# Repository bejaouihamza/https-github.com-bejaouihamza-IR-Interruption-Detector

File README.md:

# 🔦 IR Interruption Detector PCB

This project is a complete PCB-based system that detects interruptions between an **IR emitter and receiver**. When an object blocks the IR beam:
- A **buzzer/speaker** is triggered,
- A **7-segment display counter** is incremented,
- A **reset button** clears the count.

The circuit is entirely based on **discrete components**, including **NE555 timers**, **CD40106**, and a **CD4033** counter/decoder. It also includes a **robust regulated power supply**, and can be used in security, object-counting, or automation systems.

---

## 📷 Schematic

---

## 🧩 PCB Layout

---

## 🧱 3D Model

---

## ⚙️ System Overview

### ➤ Power Supply
The power input is **230V AC**, stepped down using a transformer and rectified via a **bridge diode**. The output is regulated to **+12V DC** using a **7812 voltage regulator**.

---

### ➤ IR Transmitter Stage

- **Components**: 2x NE555 + TSAL4400 IR LED
- The first NE555 generates a **square wave** (~38 kHz), modulated by the second NE555 to create an **amplitude-modulated IR beam**.
- Transistor **Q1** amplifies the signal and drives the IR LED with enough current.

---

### ➤ IR Receiver & Detection

- **TSOP2254** is used to receive the modulated IR beam.
- Its digital output goes **LOW** when it detects the 38 kHz signal.
- When an interruption occurs (e.g. hand/object blocks the beam), the output goes **HIGH**, triggering further stages.

---

### ➤ Signal Conditioning & Alarm Logic

- NE555 (U6) is configured in a monostable mode.
- CD40106 Schmitt triggers (U2, U3) are used for **clean signal shaping** and logic handling.
- This ensures only valid interruptions trigger the output.

---

### ➤ Output Stage

- A speaker or buzzer (AST-1732MR-R) is triggered via transistor Q3.
- An LED also indicates the alarm visually.

---

### ➤ Counting Stage

- A **CD4033B** 7-segment BCD counter increments with each IR interruption.
- A **D168K** display shows the count.
- A reset button allows clearing the count manually.

---

## 🔁 Workflow Summary

1. **Idle**: IR signal is received, no object interrupting.
2. **Interrupt**: Object breaks the beam → TSOP output goes HIGH.
3. **Detection**: NE555 monostable timer triggers.
4. **Alarm**: Buzzer sounds + 7segments Display increments count.
5. **Reset**: Pressing the reset button clears the counter.

---

## 🧰 Bill of Materials (BOM)

| Component     | Quantity | Notes                              |
|---------------|----------|------------------------------------|
| NE555         | 3        | Signal modulation and detection    |
| TSOP2254      | 1        | IR receiver                        |
| TSAL4400      | 1        | IR LED                             |
| CD40106       | 1        | Schmitt trigger inverter           |
| CD4033B       | 1        | BCD Counter                        |
| D168K         | 1        | 7-Segment Display                  |
| AST-1732MR-R  | 1        | Buzzer/Speaker                     |
| Q1, Q2, Q3    | 3        | NPN transistors                    |
| TP4056        | 1 (opt.) | Optional for battery version       |
| AMS1117-3.3   | 1 (opt.) | Optional for low-voltage designs   |

---

## 🔧 Tools Used

- **KiCad 9** for schematic and PCB design
- **Open source components**
- **Through-hole components **

---

## 🧠 Author

Designed by **Bejaoui Hamza**  
Date: **18 June 2025**  
Project name: `IR Interruption Detector`

---

## 📂 License

This project is open-source under the [MIT License](LICENSE).

---

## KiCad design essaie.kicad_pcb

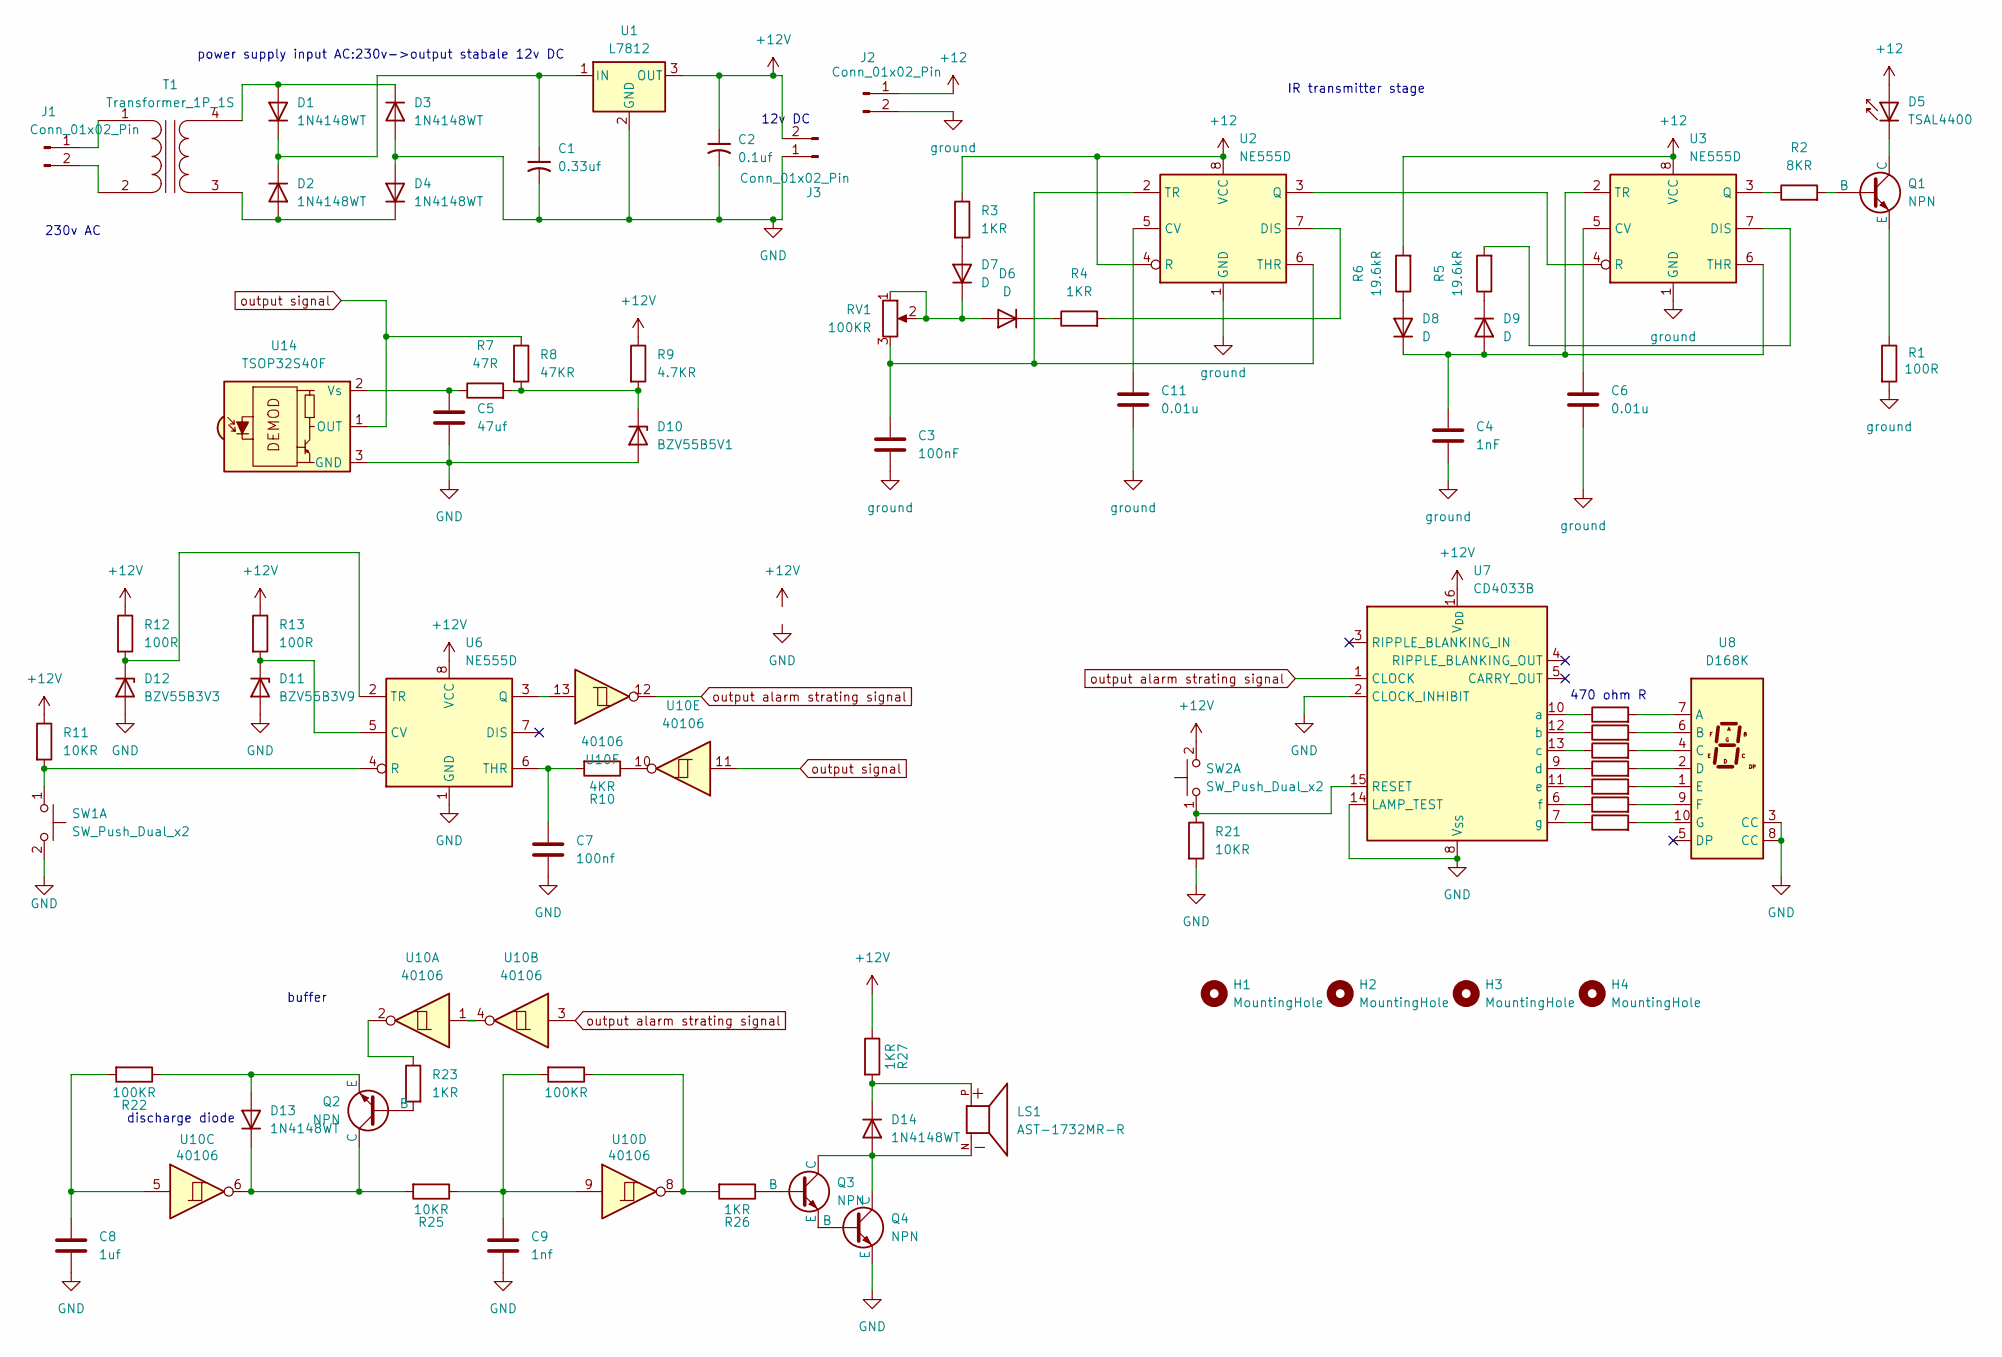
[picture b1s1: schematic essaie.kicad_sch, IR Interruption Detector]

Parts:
C1: 0.33uf; CP_Radial_D5.0mm_P2.50mm
C2: 0.1uf; CP_Radial_D5.0mm_P2.50mm
C3: 100nF; CP_Radial_D5.0mm_P2.50mm
C4: 1nF; CP_Radial_D4.0mm_P1.50mm
C5: 47uf; CP_Radial_D8.0mm_P3.50mm
C6, C11: 0.01u; CP_Radial_D4.0mm_P1.50mm
C7: 100nf; CP_Radial_D5.0mm_P2.50mm
C8: 1uf; CP_Radial_D5.0mm_P2.50mm
C9: 1nf; CP_Radial_D5.0mm_P2.50mm
D1, D2, D3, D4: 1N4148WT; D_5W_P10.16mm_Horizontal
D5: TSAL4400; LED_D3.0mm_IRBlack
D6, D7, D8, D9: D; D_DO-35_SOD27_P10.16mm_Horizontal
D10: BZV55B5V1; D_DO-35_SOD27_P10.16mm_Horizontal
D11: BZV55B3V9; D_DO-35_SOD27_P10.16mm_Horizontal
D12: BZV55B3V3; D_DO-35_SOD27_P10.16mm_Horizontal
D13, D14: 1N4148WT; D_DO-35_SOD27_P10.16mm_Horizontal
H1, H2, H3, H4: MountingHole; MountingHole_2.5mm_Pad_Via
J1, J2, J3: Conn_01x02_Pin; JST_EH_B2B-EH-A_1x02_P2.50mm_Vertical
LS1: AST-1732MR-R; SPKR_AST-1732MR-R; PARTREV C
Q1, Q2, Q3, Q4: NPN; TO-92_Inline
R1, R12, R13: 100R; R_Axial_DIN0207_L6.3mm_D2.5mm_P7.62mm_Horizontal
R2: 8KR; R_Axial_DIN0207_L6.3mm_D2.5mm_P7.62mm_Horizontal
R3, R4, R23, R26, R27: 1KR; R_Axial_DIN0207_L6.3mm_D2.5mm_P7.62mm_Horizontal
R5, R6: 19.6kR; R_Axial_DIN0207_L6.3mm_D2.5mm_P7.62mm_Horizontal
R7: 47R; R_Axial_DIN0207_L6.3mm_D2.5mm_P7.62mm_Horizontal
R8: 47KR; R_Axial_DIN0207_L6.3mm_D2.5mm_P7.62mm_Horizontal
R9: 4.7KR; R_Axial_DIN0207_L6.3mm_D2.5mm_P7.62mm_Horizontal
R10: 4KR; R_Axial_DIN0207_L6.3mm_D2.5mm_P7.62mm_Horizontal
R11, R21, R25: 10KR; R_Axial_DIN0207_L6.3mm_D2.5mm_P7.62mm_Horizontal
R14, R15, R16, R17, R18, R19, R20: R; R_Axial_DIN0207_L6.3mm_D2.5mm_P7.62mm_Horizontal
R22, R24: 100KR; R_Axial_DIN0207_L6.3mm_D2.5mm_P7.62mm_Horizontal
RV1: 100KR; Potentiometer_Bourns_3266W_Vertical
SW1, SW2: SW_Push_Dual_x2; SW_FSM8JH
T1: Transformer_1P_1S; Transformer_37x44
U1: L7812; TO-220-3_Vertical
U2, U3, U6: NE555D; DIP-8_W7.62mm
U7: CD4033B; DIP-16_W7.62mm
U8: D168K; D1X8K
U10: 40106; DIP-14_W10.16mm
U14: TSOP32S40F; Vishay_MOLD-3Pin

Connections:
+12: D5.2 (A), J2.1, R3.1, R6.2, U2.4 (R), U2.8 (VCC), U3.8 (VCC)
+12V: C2.1, J3.2, R9.1, R11.1, R12.1, R13.1, R27.1, SW2.2 (D), U1.3 (OUT), U6.8 (VCC), U7.16 (V_{DD})
GND: C1.2, C2.2, C5.2, C7.2, C8.2, C9.2, D3.2 (A), D4.2 (A), D10.2 (A), D11.2 (A), D12.2 (A), J3.1, Q4.3 (E), R21.2, SW1.2 (D), U1.2 (GND), U6.1 (GND), U7.2 (CLOCK_INHIBIT), U7.8 (V_{SS}), U7.14 (LAMP_TEST), U8.3 (CC), U8.8 (CC), U14.3 (GND)
unnamed: C8.1, R22.2, U10.5
unnamed: C9.1, R24.2, R25.1, U10.9
unnamed: D1.2 (A), D3.1 (K), T1.4 (SB)
unnamed: C1.1, D1.1 (K), D2.1 (K), U1.1 (IN)
unnamed: D2.2 (A), D4.1 (K), T1.3 (SA)
unnamed: D5.1 (K), Q1.1 (C)
unnamed: D6.2 (A), D7.1 (K), RV1.1, RV1.2
unnamed: D6.1 (K), R4.1
unnamed: D7.2 (A), R3.2
unnamed: D8.2 (A), R6.1
unnamed: C4.1, D8.1 (K), D9.2 (A), U3.2 (TR), U3.6 (THR)
unnamed: D9.1 (K), R5.1
unnamed: D10.1 (K), R7.2, R8.2, R9.2
unnamed: D11.1 (K), R13.2, U6.5 (CV)
unnamed: D12.1 (K), R12.2, U6.2 (TR)
unnamed: D13.2 (A), Q2.3 (E), R22.1
unnamed: D13.1 (K), Q2.1 (C), R25.2, U10.6
unnamed: D14.2 (A), LS1.N, Q3.1 (C), Q4.1 (C)
unnamed: D14.1 (K), LS1.P, R27.2
unnamed: J1.1, T1.1 (AA)
unnamed: J1.2, T1.2 (AB)
unnamed: Q1.2 (B), R2.2
unnamed: Q1.3 (E), R1.1
unnamed: Q2.2 (B), R23.2
unnamed: Q3.2 (B), R26.1
unnamed: Q3.3 (E), Q4.2 (B)
unnamed: R10.1, U10.10
unnamed: R23.1, U10.2
unnamed: R24.1, R26.2, U10.8
unnamed: R11.2, SW1.1 (C), U6.4 (R)
unnamed: R21.1, SW2.1 (C), U7.15 (RESET)
unnamed: C11.1, U2.5 (CV)
unnamed: R4.2, U2.7 (DIS)
unnamed: U2.3 (Q), U3.4 (R)
unnamed: C3.1, RV1.3, U2.2 (TR), U2.6 (THR)
unnamed: C6.1, U3.5 (CV)
unnamed: R5.2, U3.7 (DIS)
unnamed: R2.1, U3.3 (Q)
unnamed: U6.3 (Q), U10.13
unnamed: C7.1, R10.2, U6.6 (THR)
unnamed: R20.1, U7.10 (a)
unnamed: R19.1, U7.12 (b)
unnamed: R18.1, U7.13 (c)
unnamed: R17.1, U7.9 (d)
unnamed: R16.1, U7.11 (e)
unnamed: R15.1, U7.6 (f)
unnamed: R14.1, U7.7 (g)
unnamed: R20.2, U8.7 (A)
unnamed: R19.2, U8.6 (B)
unnamed: R18.2, U8.4 (C)
unnamed: R17.2, U8.2 (D)
unnamed: R16.2, U8.1 (E)
unnamed: R15.2, U8.9 (F)
unnamed: R14.2, U8.10 (G)
unnamed: U10.1, U10.4
unnamed: C5.1, R7.1, U14.2 (Vs)
ground: C3.2, C4.2, C6.2, C11.2, J2.2, R1.2, U2.1 (GND), U3.1 (GND)
output alarm strating signal: U7.1 (CLOCK), U10.3, U10.12
output signal: R8.1, U10.11, U14.1 (OUT)

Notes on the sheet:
12v DC
buffer
230v AC
IR transmitter stage
discharge diode
470 ohm R
power supply input AC:230v->output stabale 12v DC

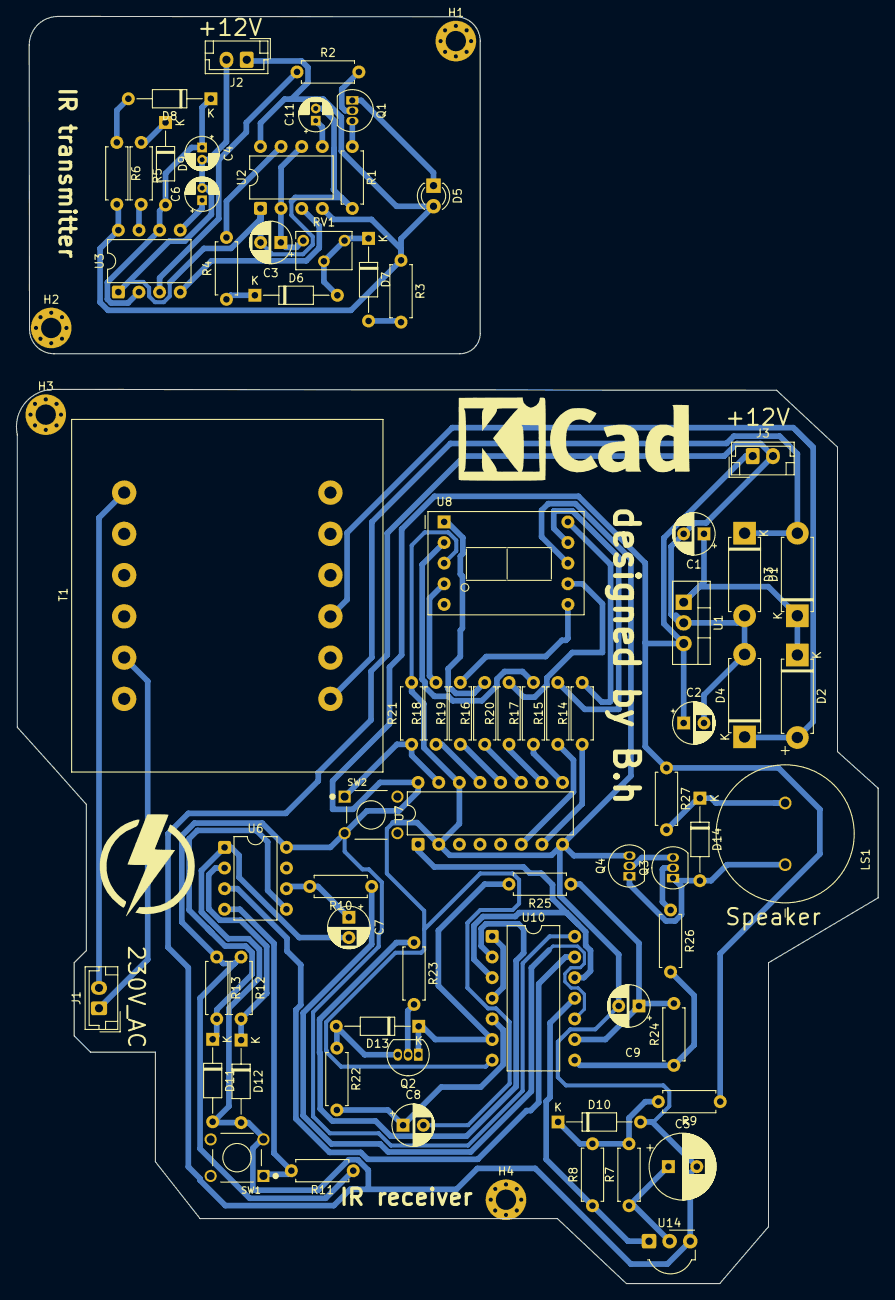
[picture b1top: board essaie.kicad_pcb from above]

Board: 2 copper layers, 106.1 x 156.0 mm, 75 parts (0 on the bottom side), 62 nets.
